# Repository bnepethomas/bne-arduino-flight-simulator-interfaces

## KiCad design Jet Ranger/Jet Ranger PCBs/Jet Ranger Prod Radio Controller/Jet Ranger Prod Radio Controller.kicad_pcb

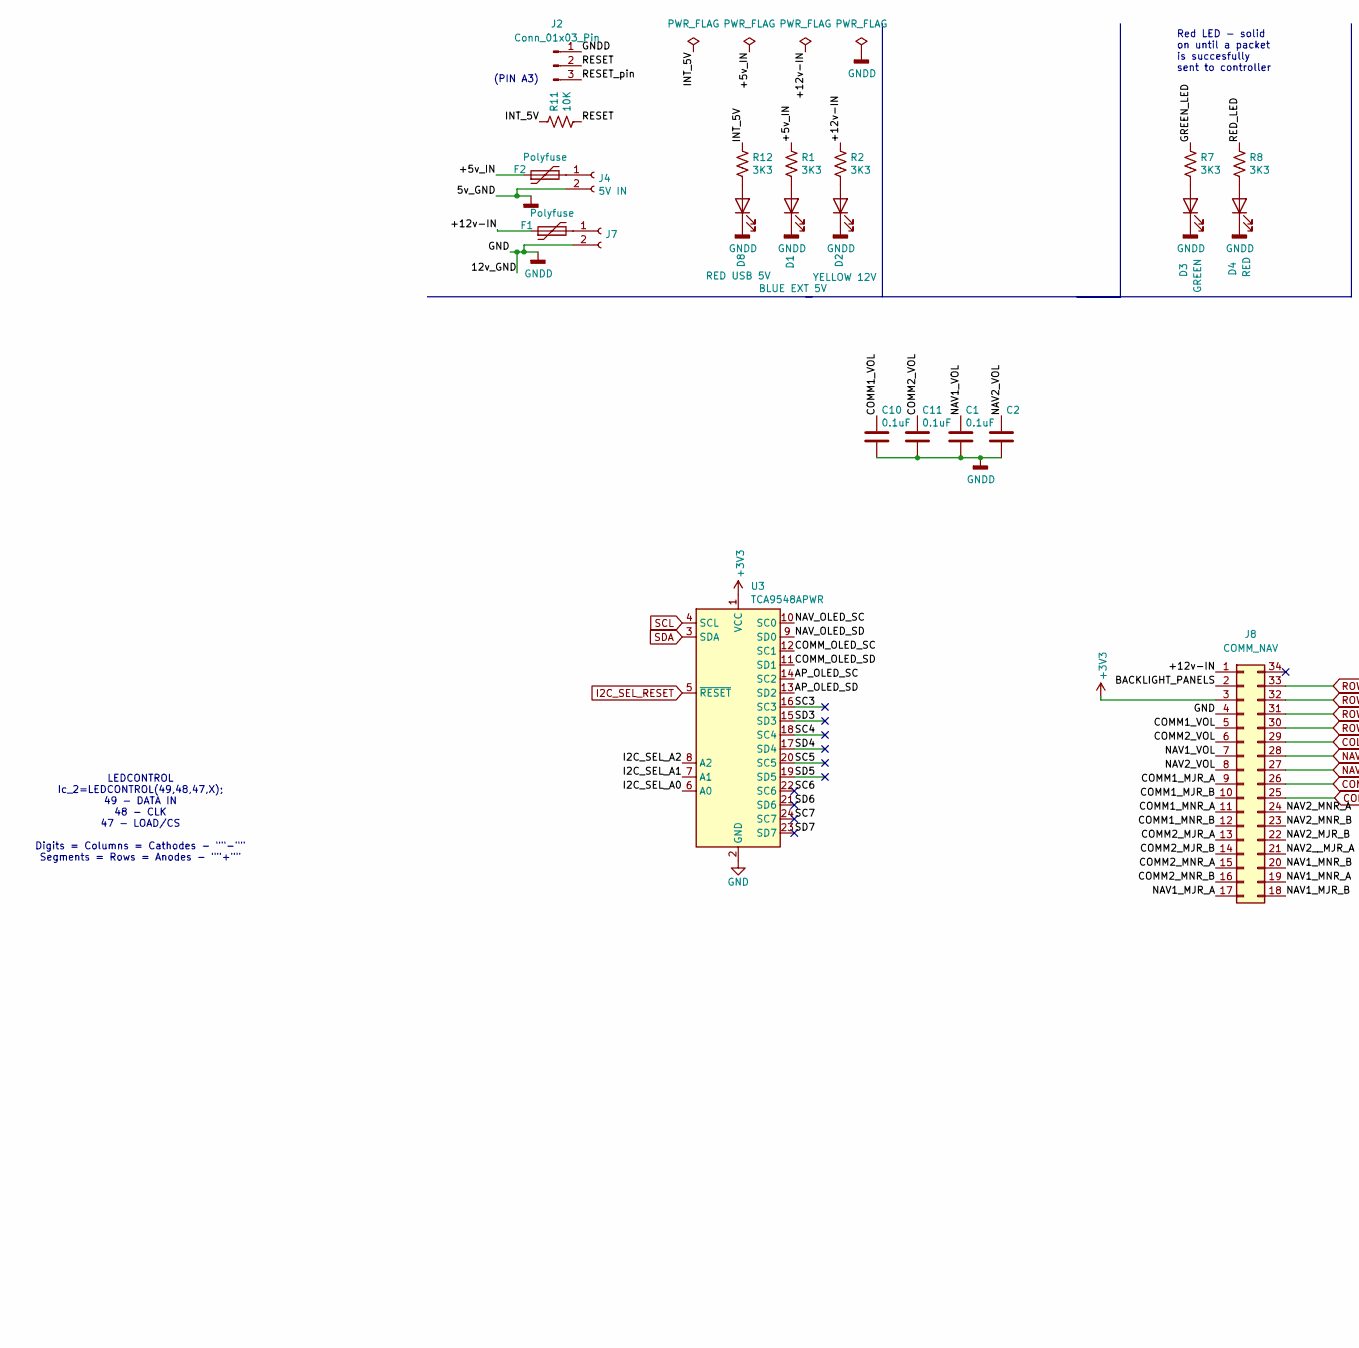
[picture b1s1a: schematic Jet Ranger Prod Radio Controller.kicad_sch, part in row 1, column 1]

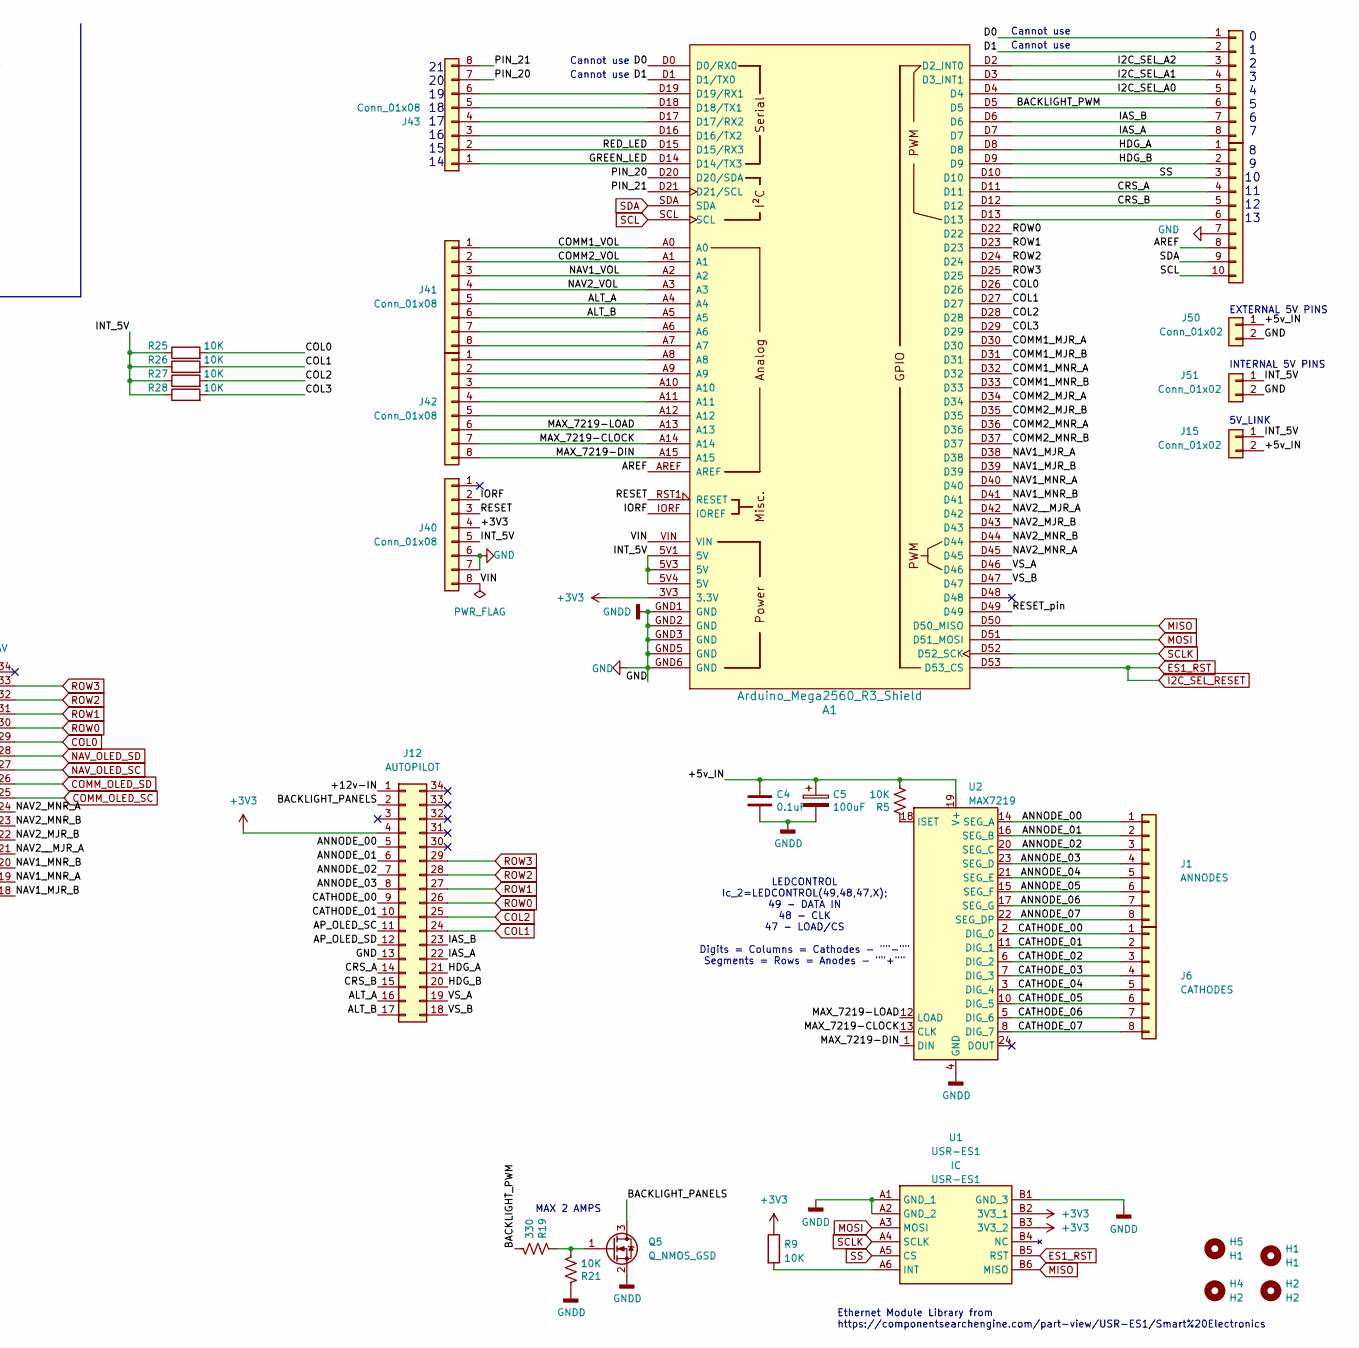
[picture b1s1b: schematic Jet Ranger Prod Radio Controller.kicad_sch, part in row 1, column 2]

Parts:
A1: Arduino_Mega2560_R3_Shield
C1, C2, C4, C10, C11: 0.1uF; C_Disc_D3.0mm_W2.0mm_P2.50mm
C5: 100uF; C_Radial_D8.0mm_H7.0mm_P3.50mm
D1: BLUE EXT 5V; LED_D3.0mm
D2: YELLOW 12V; LED_D3.0mm
D3: GREEN; LED_D3.0mm
D4: RED; LED_D3.0mm
D8: RED USB 5V; LED_D3.0mm
F1, F2: Polyfuse; Fuse_Littelfuse_395Series
H1, H5: H1; MountingHole_3.2mm_M3
H2, H4: H2; MountingHole_3.2mm_M3
J1: ANNODES; PinHeader_1x08_P2.54mm_Vertical
J2: Conn_01x03_Pin; PinHeader_1x03_P2.54mm_Vertical
J4: 5V IN; BarrelJack_Horizontal
J6: CATHODES; PinHeader_1x08_P2.54mm_Vertical
J7: STEPPER IN 12-20VDC; BarrelJack_Horizontal
J8: COMM_NAV; IDC-Header_2x17_P2.54mm_Vertical
J12: AUTOPILOT; IDC-Header_2x17_P2.54mm_Vertical
J15, J50, J51: Conn_01x02; PinHeader_1x02_P2.54mm_Vertical
J40, J41, J42, J43, J44: Conn_01x08; PinHeader_1x08_P2.54mm_Vertical
J45: Conn_01x10; PinHeader_1x10_P2.54mm_Vertical
Q5: Q_NMOS_GSD; TO-220-3_Vertical
R1, R2, R7, R8, R12: 3K3; R_Axial_DIN0207_L6.3mm_D2.5mm_P2.54mm_Vertical
R5, R9, R11, R21, R25, R26, R27, R28: 10K; R_Axial_DIN0207_L6.3mm_D2.5mm_P2.54mm_Vertical
R19: 330; R_Axial_DIN0207_L6.3mm_D2.5mm_P2.54mm_Vertical
U1: USR-ES1; USRES1; Manufacturer_Part_Number USR-ES1
U2: MAX7219; DIP-24_W7.62mm_LongPads
U3: TCA9548APWR; AllieExpress_TCA9548A

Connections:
+3V3: A1.3V3 (3.3V), J8.3, J12.4, J40.4, R9.1, U1.B2 (3V3_1), U1.B3 (3V3_2), U3.1 (VCC)
/+5v_IN: C4.1, C5.1, F2.1, J15.2, J50.1, R1.1, R5.2, U2.19 (V+)
/+12v-IN: F1.1, J8.1, J12.1, R2.1
/ALT_A: A1.A4, J12.16, J41.5
/ALT_B: A1.A5, J12.17, J41.6
/ANNODE_00: J1.1, J12.5, U2.14 (SEG_A)
/ANNODE_01: J1.2, J12.6, U2.16 (SEG_B)
/ANNODE_02: J1.3, J12.7, U2.20 (SEG_C)
/ANNODE_03: J1.4, J12.8, U2.23 (SEG_D)
/ANNODE_04: J1.5, U2.21 (SEG_E)
/ANNODE_05: J1.6, U2.15 (SEG_F)
/ANNODE_06: J1.7, U2.17 (SEG_G)
/ANNODE_07: J1.8, U2.22 (SEG_DP)
/AP_OLED_SC: J12.11, U3.14 (SC2)
/AP_OLED_SD: J12.12, U3.13 (SD2)
/AREF: A1.AREF, J45.8
/BACKLIGHT_PANELS: J8.2, J12.2, Q5.3 (D)
/BACKLIGHT_PWM: A1.D5, J44.6, R19.2
/CATHODE_00: J6.1, J12.9, U2.2 (DIG_0)
/CATHODE_01: J6.2, J12.10, U2.11 (DIG_1)
/CATHODE_02: J6.3, U2.6 (DIG_2)
/CATHODE_03: J6.4, U2.7 (DIG_3)
/CATHODE_04: J6.5, U2.3 (DIG_4)
/CATHODE_05: J6.6, U2.10 (DIG_5)
/CATHODE_06: J6.7, U2.5 (DIG_6)
/CATHODE_07: J6.8, U2.8 (DIG_7)
/COL3: A1.D29, R28.2
/COMM1_MJR_A: A1.D30, J8.9
/COMM1_MJR_B: A1.D31, J8.10
/COMM1_MNR_A: A1.D32, J8.11
/COMM1_MNR_B: A1.D33, J8.12
/COMM1_VOL: A1.A0, C10.1, J8.5, J41.1
/COMM2_MJR_A: A1.D34, J8.13
/COMM2_MJR_B: A1.D35, J8.14
/COMM2_MNR_A: A1.D36, J8.15
/COMM2_MNR_B: A1.D37, J8.16
/COMM2_VOL: A1.A1, C11.1, J8.6, J41.2
/CRS_A: A1.D11, J12.14, J45.4
/CRS_B: A1.D12, J12.15, J45.5
/D0: A1.D0 (D0/RX0), J44.1
/D1: A1.D1 (D1/TX0), J44.2
/GREEN_LED: A1.D14 (D14/TX3), J43.1, R7.1
/HDG_A: A1.D8, J12.21, J45.1
/HDG_B: A1.D9, J12.20, J45.2
/I2C_SEL_A0: A1.D4, J44.5, U3.6 (A0)
/I2C_SEL_A1: A1.D3 (D3_INT1), J44.4, U3.7 (A1)
/I2C_SEL_A2: A1.D2 (D2_INT0), J44.3, U3.8 (A2)
/IAS_A: A1.D7, J12.22, J44.8
/IAS_B: A1.D6, J12.23, J44.7
/INT_5V: A1.5V1 (5V), A1.5V3 (5V), A1.5V4 (5V), J15.1, J40.5, J51.1, R11.1, R12.1, R25.1, R26.1, R27.1, R28.1
/IORF: A1.IORF (IOREF), J40.2
/MAX_7219-CLOCK: A1.A14, J42.7, U2.13 (CLK)
/MAX_7219-DIN: A1.A15, J42.8, U2.1 (DIN)
/MAX_7219-LOAD: A1.A13, J42.6, U2.12 (LOAD)
/NAV1_MJR_A: A1.D38, J8.17
/NAV1_MJR_B: A1.D39, J8.18
/NAV1_MNR_A: A1.D40, J8.19
/NAV1_MNR_B: A1.D41, J8.20
/NAV1_VOL: A1.A2, C1.1, J8.7, J41.3
/NAV2_MJR_B: A1.D43, J8.22
/NAV2_MNR_A: A1.D45, J8.24
/NAV2_MNR_B: A1.D44, J8.23
/NAV2_VOL: A1.A3, C2.1, J8.8, J41.4
/NAV2__MJR_A: A1.D42, J8.21
/PIN_20: A1.D20 (D20/SDA), J43.7
/PIN_21: A1.D21 (D21/SCL), J43.8
/RED_LED: A1.D15 (D15/RX3), J43.2, R8.1
/RESET: A1.RST1 (RESET), J2.2, J40.3, R11.2
/RESET_pin: A1.D49, J2.3
/SC3: U3.16 (SC3)
/SC4: U3.18 (SC4)
/SC5: U3.20 (SC5)
/SC6: U3.22 (SC6)
/SC7: U3.24 (SC7)
/SD3: U3.15 (SD3)
/SD4: U3.17 (SD4)
/SD5: U3.19 (SD5)
/SD6: U3.21 (SD6)
/SD7: U3.23 (SD7)
/VIN: A1.VIN, J40.8
/VS_A: A1.D46, J12.19
/VS_B: A1.D47, J12.18
COL0: A1.D26, J8.29, R25.2
COL1: A1.D27, J12.24, R26.2
COL2: A1.D28, J12.25, R27.2
COMM_OLED_SC: J8.25, U3.12 (SC1)
COMM_OLED_SD: J8.26, U3.11 (SD1)
ES1_RST: A1.D53 (D53_CS), U1.B5 (RST), U3.5 (~RESET)
GND: A1.GND1 (GND), A1.GND2 (GND), A1.GND3 (GND), A1.GND5 (GND), A1.GND6 (GND), C1.2, C2.2, C4.2, C5.2, C10.2, C11.2, D1.1 (K), D2.1 (K), D3.1 (K), D4.1 (K), D8.1 (K), J2.1, J4.2, J7.2, J8.4, J12.13, J40.6, J40.7, J45.7, J50.2, J51.2, Q5.2 (S), R21.1, U1.A1 (GND_1), U1.A2 (GND_2), U1.B1 (GND_3), U2.4 (GND), U2.9 (GND), U3.2 (GND)
MISO: A1.D50 (D50_MISO), U1.B6 (MISO)
MOSI: A1.D51 (D51_MOSI), U1.A3 (MOSI)
NAV_OLED_SC: J8.27, U3.10 (SC0)
NAV_OLED_SD: J8.28, U3.9 (SD0)
unnamed: A1.D16 (D16/TX2), J43.3
unnamed: A1.D17 (D17/RX2), J43.4
unnamed: A1.D18 (D18/TX1), J43.5
unnamed: A1.D19 (D19/RX1), J43.6
unnamed: D1.2 (A), R1.2
unnamed: D2.2 (A), R2.2
unnamed: D3.2 (A), R7.2
unnamed: D4.2 (A), R8.2
unnamed: D8.2 (A), R12.2
unnamed: F2.2, J4.1
unnamed: F1.2, J7.1
unnamed: A1.A6, J41.7
unnamed: A1.A7, J41.8
unnamed: A1.A8, J42.1
unnamed: A1.A9, J42.2
unnamed: A1.A10, J42.3
unnamed: A1.A11, J42.4
unnamed: A1.A12, J42.5
unnamed: A1.D13, J45.6
unnamed: Q5.1 (G), R19.1, R21.2
unnamed: R9.2, U1.A6 (INT)
unnamed: R5.1, U2.18 (ISET)
ROW0: A1.D22, J8.30, J12.26
ROW1: A1.D23, J8.31, J12.27
ROW2: A1.D24, J8.32, J12.28
ROW3: A1.D25, J8.33, J12.29
SCL: A1.SCL, J45.10, U3.4 (SCL)
SCLK: A1.D52 (D52_SCK), U1.A4 (SCLK)
SDA: A1.SDA, J45.9, U3.3 (SDA)
SS: A1.D10, J45.3, U1.A5 (CS)

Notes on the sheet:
MAX 2 AMPS
INTERNAL 5V PINS
Ethernet Module Library from https://componentsearchengine.com/part-view/USR-ES1/Smart%20Electronics
LEDCONTROL Ic_2=LEDCONTROL(49,48,47,X); 49 - DATA IN 48 - CLK 47 - LOAD/CS Digits = Columns = Cathodes - ""-"" Segments = Rows = Anodes - ""+""
Cannot use
(PIN A3)
0 1 2 3 4 5 6 7
Red LED - solid on until a packet is succesfully sent to controller
5V_LINK
21 20 19 18 17 16 15 14
EXTERNAL 5V PINS
8 9 10 11 12 13

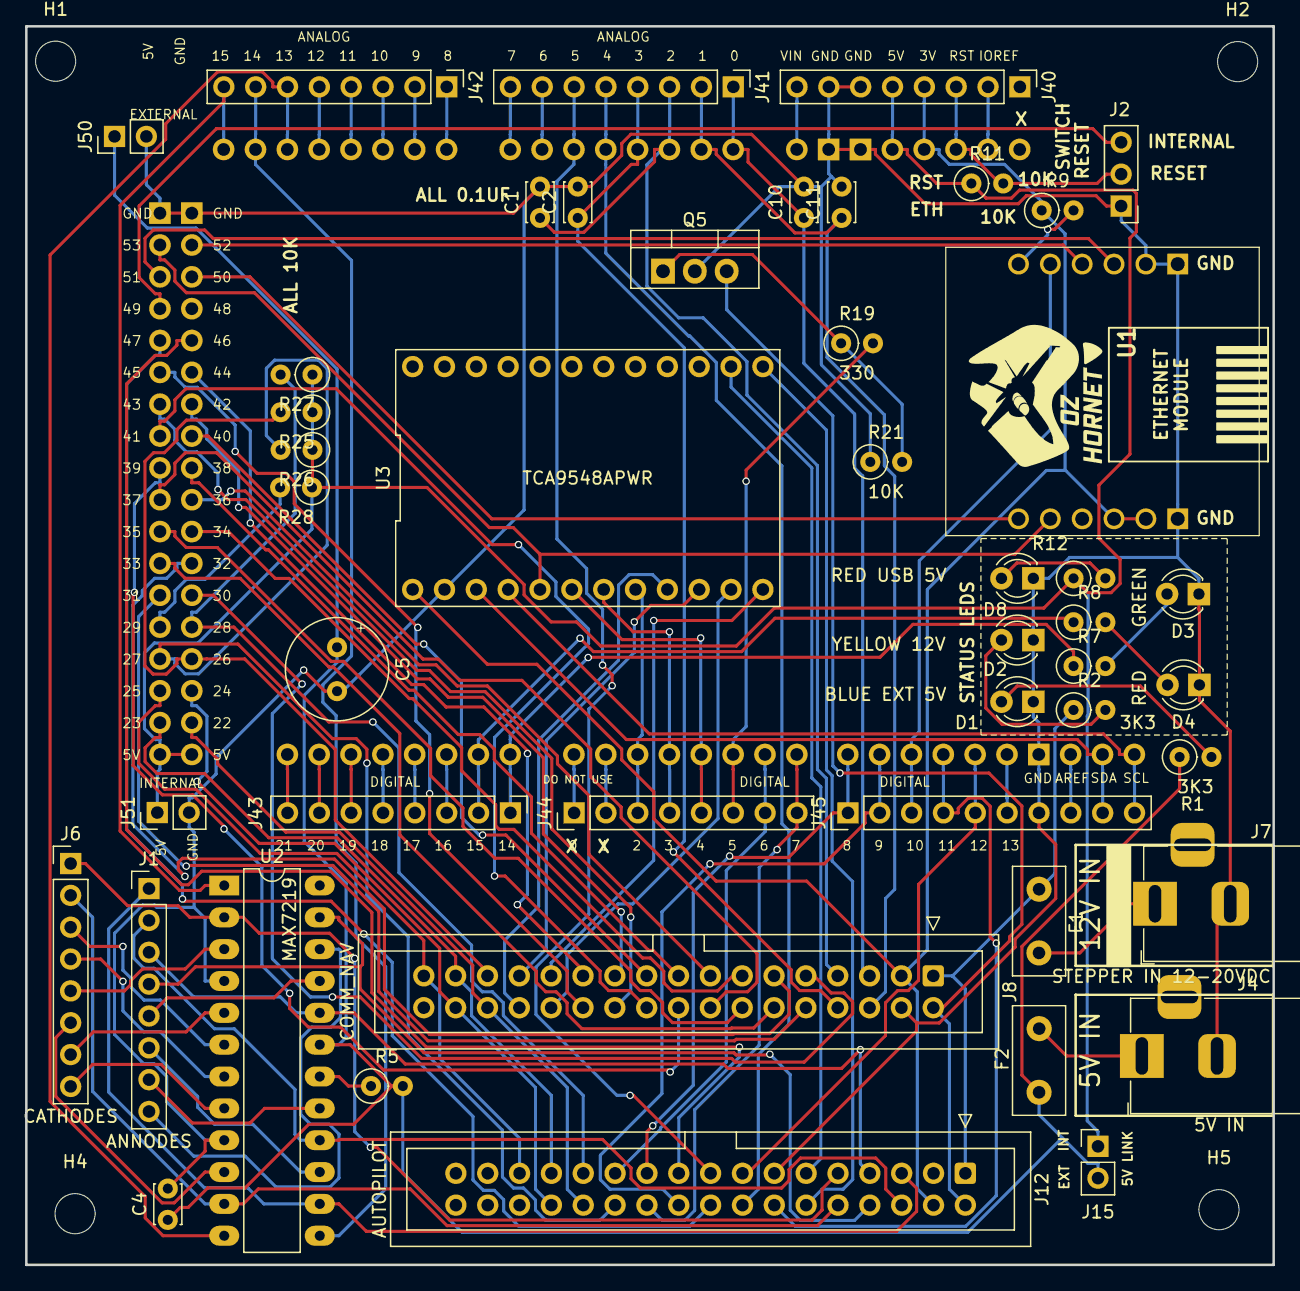
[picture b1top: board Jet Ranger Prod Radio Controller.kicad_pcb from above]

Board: 2 copper layers, 99.5 x 98.8 mm, 52 parts (0 on the bottom side), 113 nets.

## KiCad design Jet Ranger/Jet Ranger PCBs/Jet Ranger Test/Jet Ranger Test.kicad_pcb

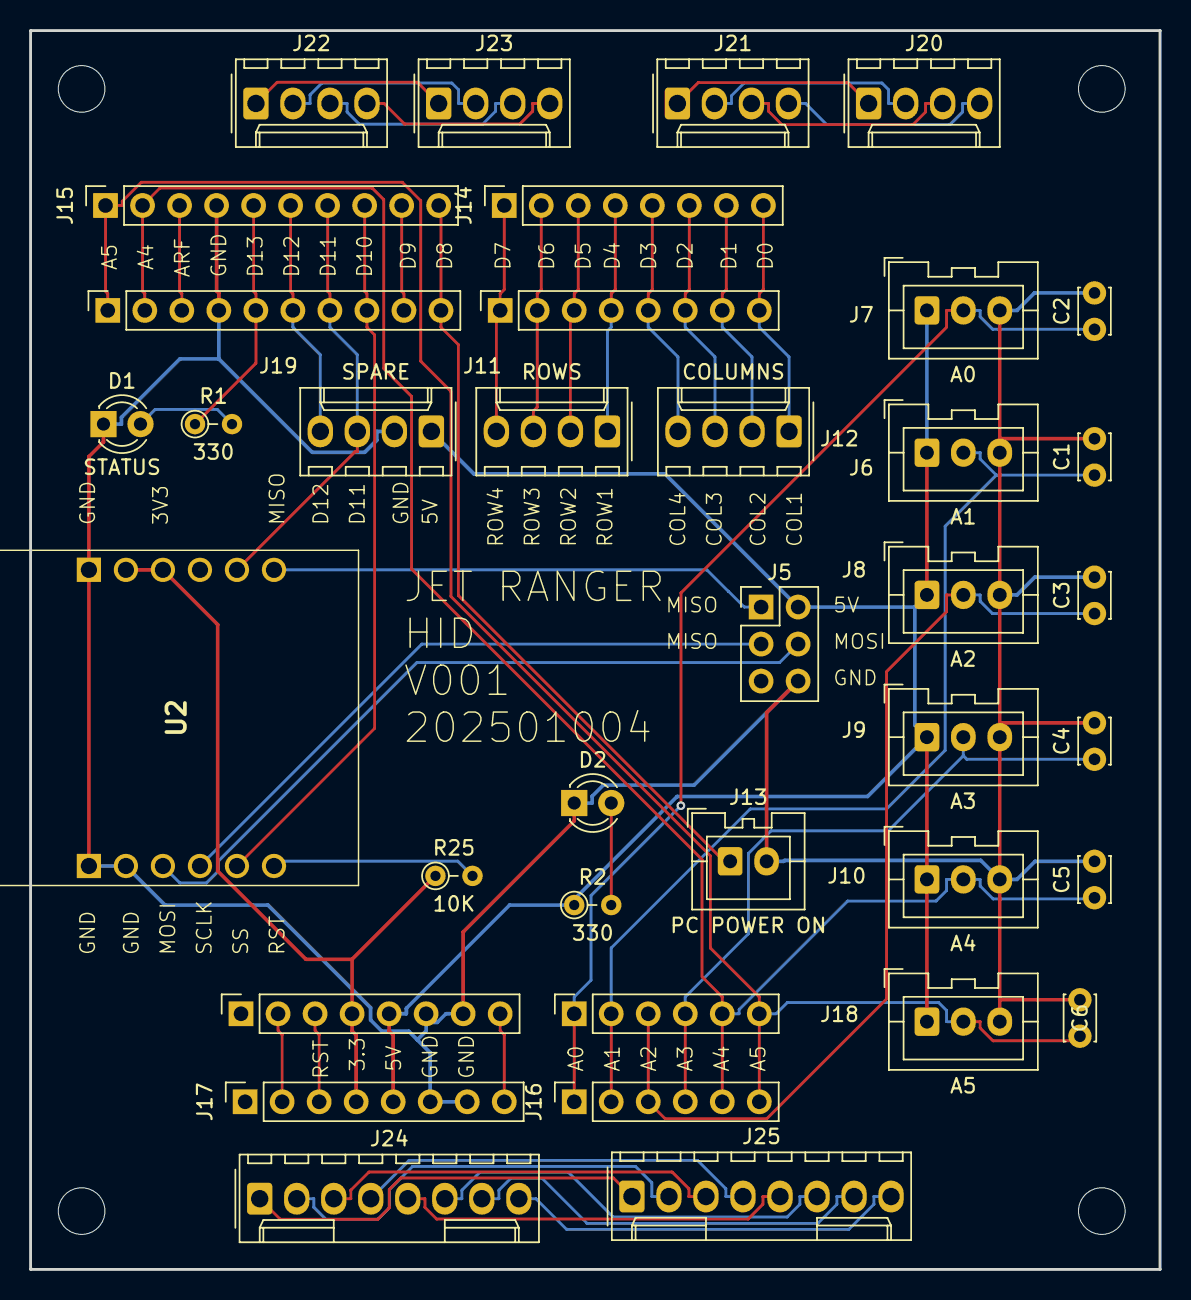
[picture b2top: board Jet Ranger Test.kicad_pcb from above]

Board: 2 copper layers, 77.5 x 85.0 mm, 41 parts (0 on the bottom side), 49 nets.

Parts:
C1, C2, C3, C4, C5, C6: 0.1uF; C_Disc_D3.0mm_W2.0mm_P2.50mm
D1: STATUS; LED_D3.0mm_FlatTop
D2: 5V; LED_D3.0mm_FlatTop
H1, H2, H3, H4: MountingHole; MountingHole_3.2mm_M3
J1, J17: Power; PinSocket_1x08_P2.54mm_Vertical
J2, J15: Digital/PWM; PinSocket_1x10_P2.54mm_Vertical
J3, J16: Analog; PinSocket_1x06_P2.54mm_Vertical
J4, J14: Digital/PWM; PinSocket_1x08_P2.54mm_Vertical
J5: ICSP; PinHeader_2x03_P2.54mm_Vertical
J6: A1; JST_XA_B03B-XASK-1_1x03_P2.50mm_Vertical
J7: A0; JST_XA_B03B-XASK-1_1x03_P2.50mm_Vertical
J8: A2; JST_XA_B03B-XASK-1_1x03_P2.50mm_Vertical
J9: A3; JST_XA_B03B-XASK-1_1x03_P2.50mm_Vertical
J10: A4; JST_XA_B03B-XASK-1_1x03_P2.50mm_Vertical
J11: ROWS; Molex_KK-254_AE-6410-04A_1x04_P2.54mm_Vertical
J12: COLUMNS; Molex_KK-254_AE-6410-04A_1x04_P2.54mm_Vertical
J13: PC POWER ON; JST_XA_B02B-XASK-1_1x02_P2.50mm_Vertical
J18: A5; JST_XA_B03B-XASK-1_1x03_P2.50mm_Vertical
J19, J20, J21, J22, J23: SPARE; Molex_KK-254_AE-6410-04A_1x04_P2.54mm_Vertical
J24, J25: SPARE; Molex_KK-254_AE-6410-08A_1x08_P2.54mm_Vertical
R1, R2: 330; R_Axial_DIN0204_L3.6mm_D1.6mm_P2.54mm_Vertical
R25: 10K; R_Axial_DIN0204_L3.6mm_D1.6mm_P2.54mm_Vertical
U2: USR-ES1; USRES1

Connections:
+3V3: J1.4, J17.4, R25.1, U2.B2 (3V3_1), U2.B3 (3V3_2)
+5V: J1.5, J5.2, J6.1, J7.1, J8.1, J9.1, J10.1, J17.5, J18.1, J19.1, R2.1
/2: J4.6, J12.3, J14.6
/4: J4.4, J11.1, J14.4
/7: J4.1, J11.4, J14.1
/8: J2.10, J13.1, J15.10
/12: J2.6, J15.6, J19.4
/13: J2.5, J15.5, R1.1
/*3: J4.5, J12.4, J14.5
/*5: J4.3, J11.2, J14.3
/*6: J4.2, J11.3, J14.2
/*9: J2.9, J15.9
/A0: C2.1, J3.1, J7.2, J16.1
/A1: C1.1, J3.2, J6.2, J16.2
/A2: C3.1, J3.3, J8.2, J16.3
/A3: C4.1, J3.4, J9.2, J16.4
/A4: C5.1, J2.2, J3.5, J10.2, J15.2, J16.5
/A5: C6.1, J2.1, J3.6, J15.1, J16.6, J18.2
/AREF: J2.3, J15.3
/COL1: J4.8, J12.1, J14.8
/COL2: J4.7, J12.2, J14.7
/IOREF: J1.2, J17.2
/~RESET: J1.3, J17.3
ES1_RST: J2.7, J15.7, J19.3, U2.B5 (RST)
GND: C1.2, C2.2, C3.2, C4.2, C5.2, C6.2, D1.1 (K), D2.1 (K), J1.6, J1.7, J2.4, J5.6, J6.3, J7.3, J8.3, J9.3, J10.3, J13.2, J15.4, J17.6, J17.7, J18.3, J19.2, U2.A1 (GND_1), U2.A2 (GND_2), U2.B1 (GND_3)
MISO: J5.1, U2.B6 (MISO)
MOSI: J5.4, U2.A3 (MOSI)
unnamed: D1.2 (A), R1.2
unnamed: D2.2 (A), R2.2
unnamed: J20.1, J21.1
unnamed: J20.2, J21.2
unnamed: J20.3, J21.3
unnamed: J20.4, J21.4
unnamed: J22.1, J23.1
unnamed: J22.2, J23.2
unnamed: J22.3, J23.3
unnamed: J22.4, J23.4
unnamed: J24.1, J25.1
unnamed: J24.2, J25.2
unnamed: J24.3, J25.3
unnamed: J24.4, J25.4
unnamed: J24.5, J25.5
unnamed: J24.6, J25.6
unnamed: J24.7, J25.7
unnamed: J24.8, J25.8
unnamed: R25.2, U2.A6 (INT)
SCLK: J5.3, U2.A4 (SCLK)
SS: J2.8, J15.8, U2.A5 (CS)
VCC: J1.8, J17.8

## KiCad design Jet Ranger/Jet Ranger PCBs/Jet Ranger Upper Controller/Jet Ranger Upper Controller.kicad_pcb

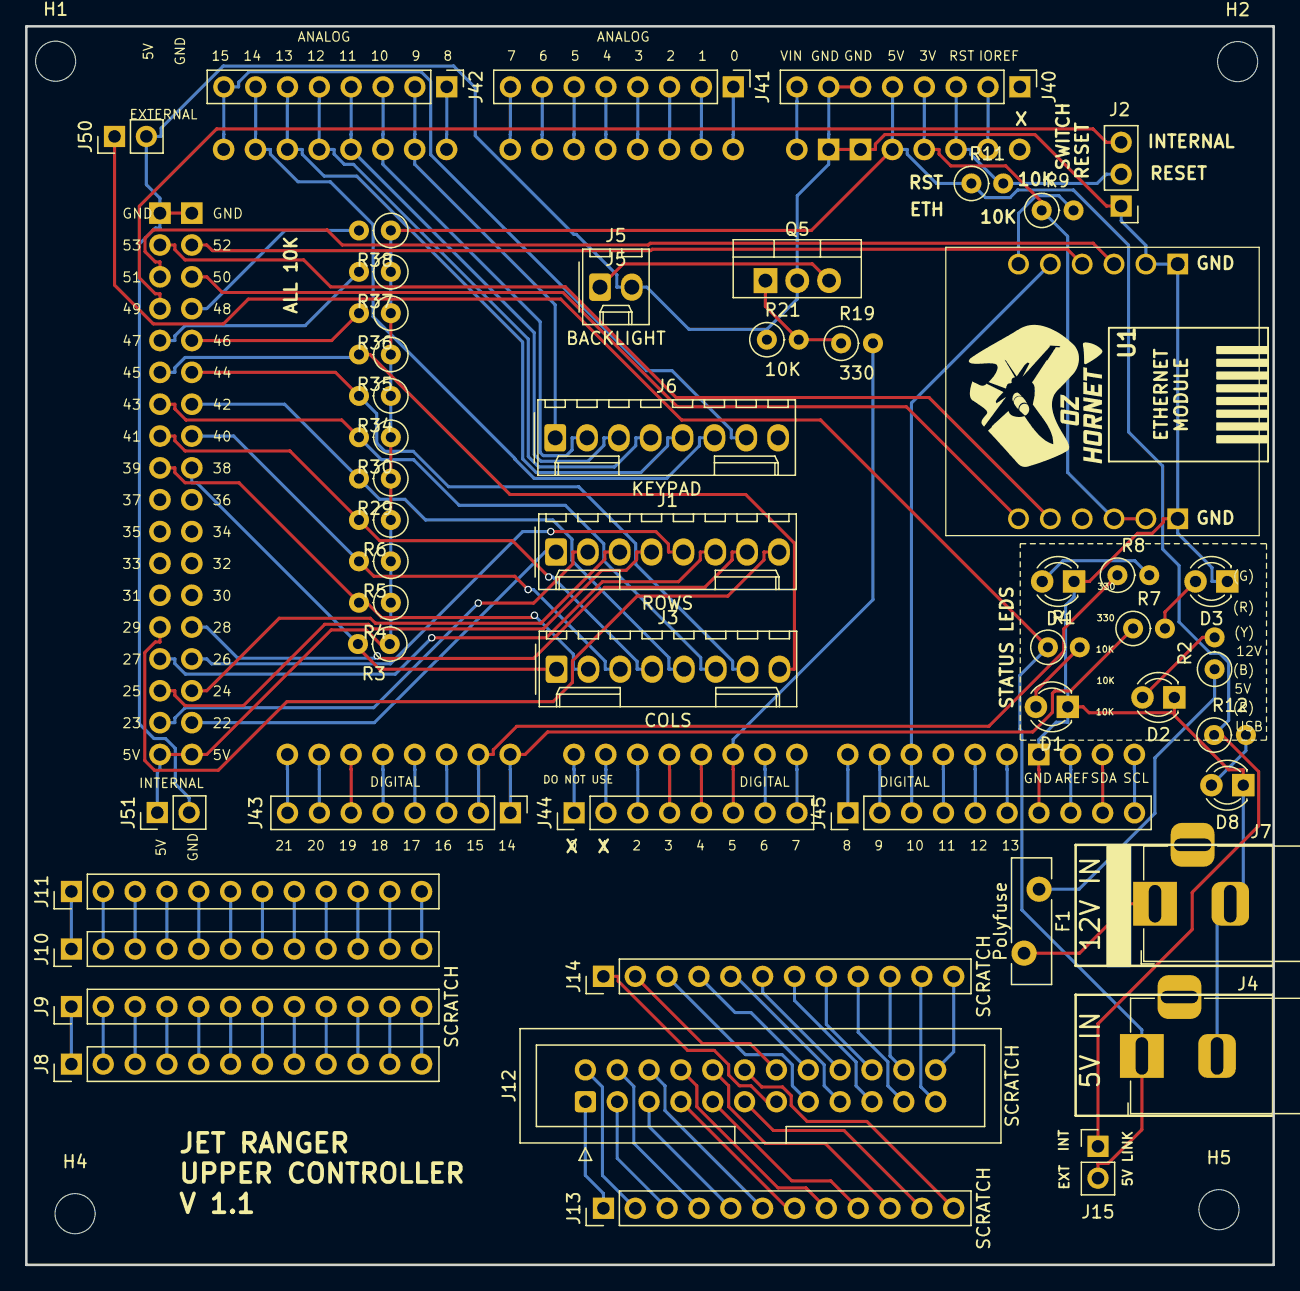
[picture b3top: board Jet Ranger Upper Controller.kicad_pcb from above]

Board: 2 copper layers, 99.5 x 98.8 mm, 56 parts (0 on the bottom side), 130 nets.

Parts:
A1: Arduino_Mega2560_R3_Shield
D1, D2, D8: LED; LED_D3.0mm
D3: GREEN; LED_D3.0mm
D4: RED; LED_D3.0mm
F1: Polyfuse; Fuse_Bourns_MF-RG400
H1, H5: H1; MountingHole_3.2mm_M3
H2, H4: H2; MountingHole_3.2mm_M3
J1: ROWS; Molex_KK-254_AE-6410-08A_1x08_P2.54mm_Vertical
J2: Conn_01x03_Pin; PinHeader_1x03_P2.54mm_Vertical
J3: COLS; Molex_KK-254_AE-6410-08A_1x08_P2.54mm_Vertical
J4: 5V IN; BarrelJack_Horizontal
J5: BACKLIGHT; Molex_KK-254_AE-6410-02A_1x02_P2.54mm_Vertical
J6: KEYPAD; Molex_KK-254_AE-6410-08A_1x08_P2.54mm_Vertical
J7: STEPPER IN 12-20VDC; BarrelJack_Horizontal
J8, J9, J10, J11, J13, J14: SCRATCH; PinHeader_1x12_P2.54mm_Vertical
J12: SCRATCH; IDC-Header_2x12_P2.54mm_Vertical
J15, J50, J51: Conn_01x02; PinHeader_1x02_P2.54mm_Vertical
J40, J41, J42, J43, J44: Conn_01x08; PinHeader_1x08_P2.54mm_Vertical
J45: Conn_01x10; PinHeader_1x10_P2.54mm_Vertical
Q5: Q_NMOS_GSD; TO-220-3_Vertical
R1, R12: 5K; R_Axial_DIN0207_L6.3mm_D2.5mm_P2.54mm_Vertical
R2, R3, R4, R5, R6, R9, R11, R21, R29, R30, R34, R35, R36, R37, R38: 10K; R_Axial_DIN0207_L6.3mm_D2.5mm_P2.54mm_Vertical
R7, R8, R19: 330; R_Axial_DIN0207_L6.3mm_D2.5mm_P2.54mm_Vertical
U1: USR-ES1; USRES1

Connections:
+3V3: A1.3V3 (3.3V), J40.4, R9.1, U1.B2 (3V3_1), U1.B3 (3V3_2)
/+5v_IN: J4.1, J15.2, J50.1, R1.1
/+12v-IN: F1.1, R2.1
/AREF: A1.AREF, J45.8
/BACKLIGHT_PANELS: J5.1, Q5.3 (D)
/BACKLIGHT_PWM: A1.D5, J44.6, R19.2
/COL0: A1.D38, J3.1, R3.2
/COL1: A1.D39, J3.2, R4.2
/COL2: A1.D40, J3.3, R5.2
/COL3: A1.D41, J3.4, R6.2
/COL4: A1.D42, J3.5, R29.2
/COL5: A1.D43, J3.6, R30.2
/COL6: A1.D44, J3.7, R34.2
/COL7: A1.D45, J3.8, R35.2
/COL8: A1.D46, R36.2
/COL9: A1.D47, R37.2
/COL10: A1.D48, R38.2
/D0: A1.D0 (D0/RX0), J44.1
/D1: A1.D1 (D1/TX0), J44.2
/GPS_TX: A1.D18 (D18/TX1), J43.5
/GREEN_LED: A1.D14 (D14/TX3), J43.1, R7.1
/INT_5V: A1.5V1 (5V), A1.5V3 (5V), A1.5V4 (5V), J15.1, J40.5, J51.1, R3.1, R4.1, R5.1, R6.1, R11.1, R12.1, R29.1, R30.1, R34.1, R35.1, R36.1, R37.1, R38.1
/IORF: A1.IORF (IOREF), J40.2
/KEYPAD_1: A1.A9, J6.1, J42.2
/KEYPAD_2: A1.A10, J6.2, J42.3
/KEYPAD_3: A1.A11, J6.3, J42.4
/KEYPAD_4: A1.A12, J6.4, J42.5
/KEYPAD_5: A1.A13, J6.5, J42.6
/KEYPAD_6: A1.A14, J6.6, J42.7
/KEYPAD_7: A1.A15, J6.7, J42.8
/PIN_20: A1.D20 (D20/SDA), J43.7
/PIN_21: A1.D21 (D21/SCL), J43.8
/RED_LED: A1.D15 (D15/RX3), J43.2, R8.1
/RESET: A1.RST1 (RESET), J2.2, J40.3, R11.2
/RESET_pin: A1.D49, J2.3
/ROW0: A1.D22, J1.1
/ROW1: A1.D23, J1.2
/ROW2: A1.D24, J1.3
/ROW3: A1.D25, J1.4
/ROW4: A1.D26, J1.5
/ROW5: A1.D27, J1.6
/ROW6: A1.D28, J1.7
/ROW7: A1.D29, J1.8
/VIN: A1.VIN, J40.8
ES1_RST: A1.D53 (D53_CS), U1.B5 (RST)
GND: A1.GND1 (GND), A1.GND2 (GND), A1.GND3 (GND), A1.GND5 (GND), A1.GND6 (GND), D1.1 (K), D2.1 (K), D3.1 (K), D4.1 (K), D8.1 (K), J2.1, J4.2, J5.2, J7.2, J40.6, J40.7, J45.7, J50.2, J51.2, Q5.2 (S), R21.1, U1.A1 (GND_1), U1.A2 (GND_2), U1.B1 (GND_3)
MISO: A1.D50 (D50_MISO), U1.B6 (MISO)
MOSI: A1.D51 (D51_MOSI), U1.A3 (MOSI)
unnamed: A1.D2 (D2_INT0), J44.3
unnamed: A1.D3 (D3_INT1), J44.4
unnamed: A1.D16 (D16/TX2), J43.3
unnamed: A1.D17 (D17/RX2), J43.4
unnamed: A1.D19 (D19/RX1), J43.6
unnamed: D1.2 (A), R1.2
unnamed: D2.2 (A), R2.2
unnamed: D3.2 (A), R7.2
unnamed: D4.2 (A), R8.2
unnamed: D8.2 (A), R12.2
unnamed: F1.2, J7.1
unnamed: J8.1, J9.1
unnamed: J8.2, J9.2
unnamed: J8.3, J9.3
unnamed: J8.4, J9.4
unnamed: J8.5, J9.5
unnamed: J8.6, J9.6
unnamed: J8.7, J9.7
unnamed: J8.8, J9.8
unnamed: J8.9, J9.9
unnamed: J8.10, J9.10
unnamed: J8.11, J9.11
unnamed: J8.12, J9.12
unnamed: J10.1, J11.1
unnamed: J10.2, J11.2
unnamed: J10.3, J11.3
unnamed: J10.4, J11.4
unnamed: J10.5, J11.5
unnamed: J10.6, J11.6
unnamed: J10.7, J11.7
unnamed: J10.8, J11.8
unnamed: J10.9, J11.9
unnamed: J10.10, J11.10
unnamed: J10.11, J11.11
unnamed: J10.12, J11.12
unnamed: J12.1, J13.1
unnamed: J12.2, J13.2
unnamed: J12.3, J13.3
unnamed: J12.4, J13.4
unnamed: J12.5, J13.5
unnamed: J12.6, J13.6
unnamed: J12.7, J13.7
unnamed: J12.8, J13.8
unnamed: J12.9, J13.9
unnamed: J12.10, J13.10
unnamed: J12.11, J13.11
unnamed: J12.12, J13.12
unnamed: J12.13, J14.1
unnamed: J12.14, J14.2
unnamed: J12.15, J14.3
unnamed: J12.16, J14.4
unnamed: J12.17, J14.5
unnamed: J12.18, J14.6
unnamed: J12.19, J14.7
unnamed: J12.20, J14.8
unnamed: J12.21, J14.9
unnamed: J12.22, J14.10
unnamed: J12.23, J14.11
unnamed: J12.24, J14.12
unnamed: A1.A0, J41.1
unnamed: A1.A1, J41.2
unnamed: A1.A2, J41.3
unnamed: A1.A3, J41.4
unnamed: A1.A4, J41.5
unnamed: A1.A5, J41.6
unnamed: A1.A6, J41.7
unnamed: A1.A7, J41.8
unnamed: A1.A8, J42.1
unnamed: A1.D4, J44.5
unnamed: A1.D6, J44.7
unnamed: A1.D7, J44.8
unnamed: A1.D8, J45.1
unnamed: A1.D9, J45.2
unnamed: A1.D11, J45.4
unnamed: A1.D12, J45.5
unnamed: A1.D13, J45.6
unnamed: Q5.1 (G), R19.1, R21.2
unnamed: R9.2, U1.A6 (INT)
SCL: A1.SCL, J45.10
SCLK: A1.D52 (D52_SCK), U1.A4 (SCLK)
SDA: A1.SDA, J45.9
SS: A1.D10, J45.3, U1.A5 (CS)

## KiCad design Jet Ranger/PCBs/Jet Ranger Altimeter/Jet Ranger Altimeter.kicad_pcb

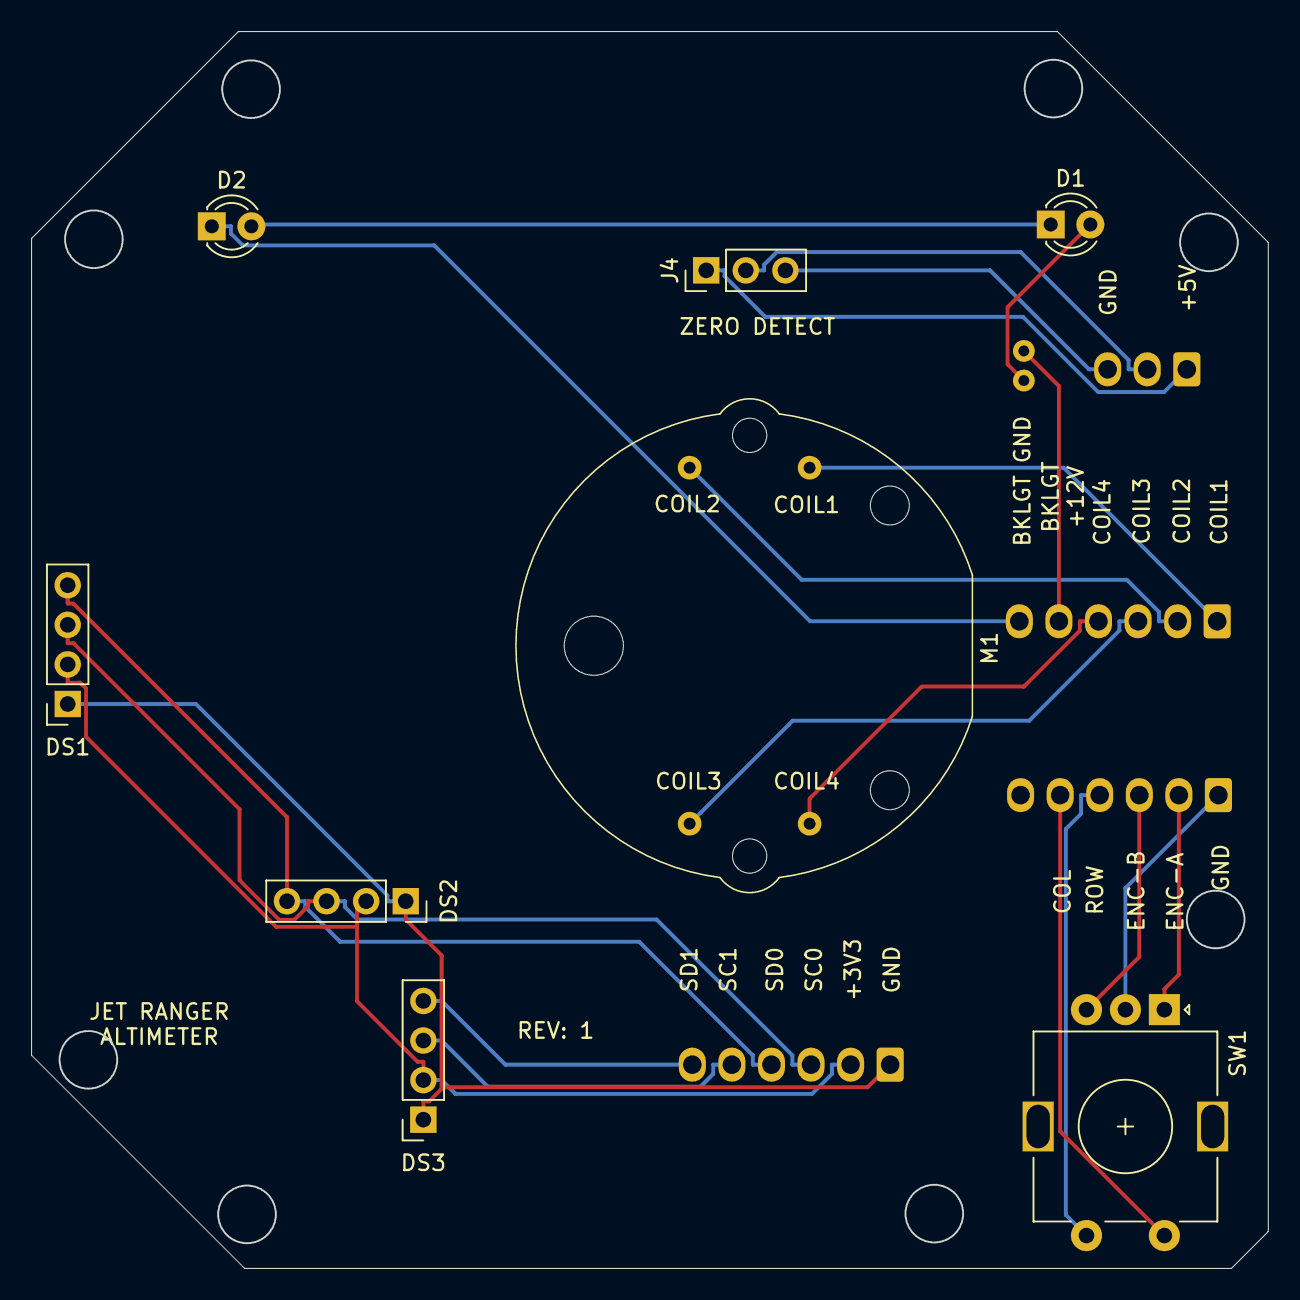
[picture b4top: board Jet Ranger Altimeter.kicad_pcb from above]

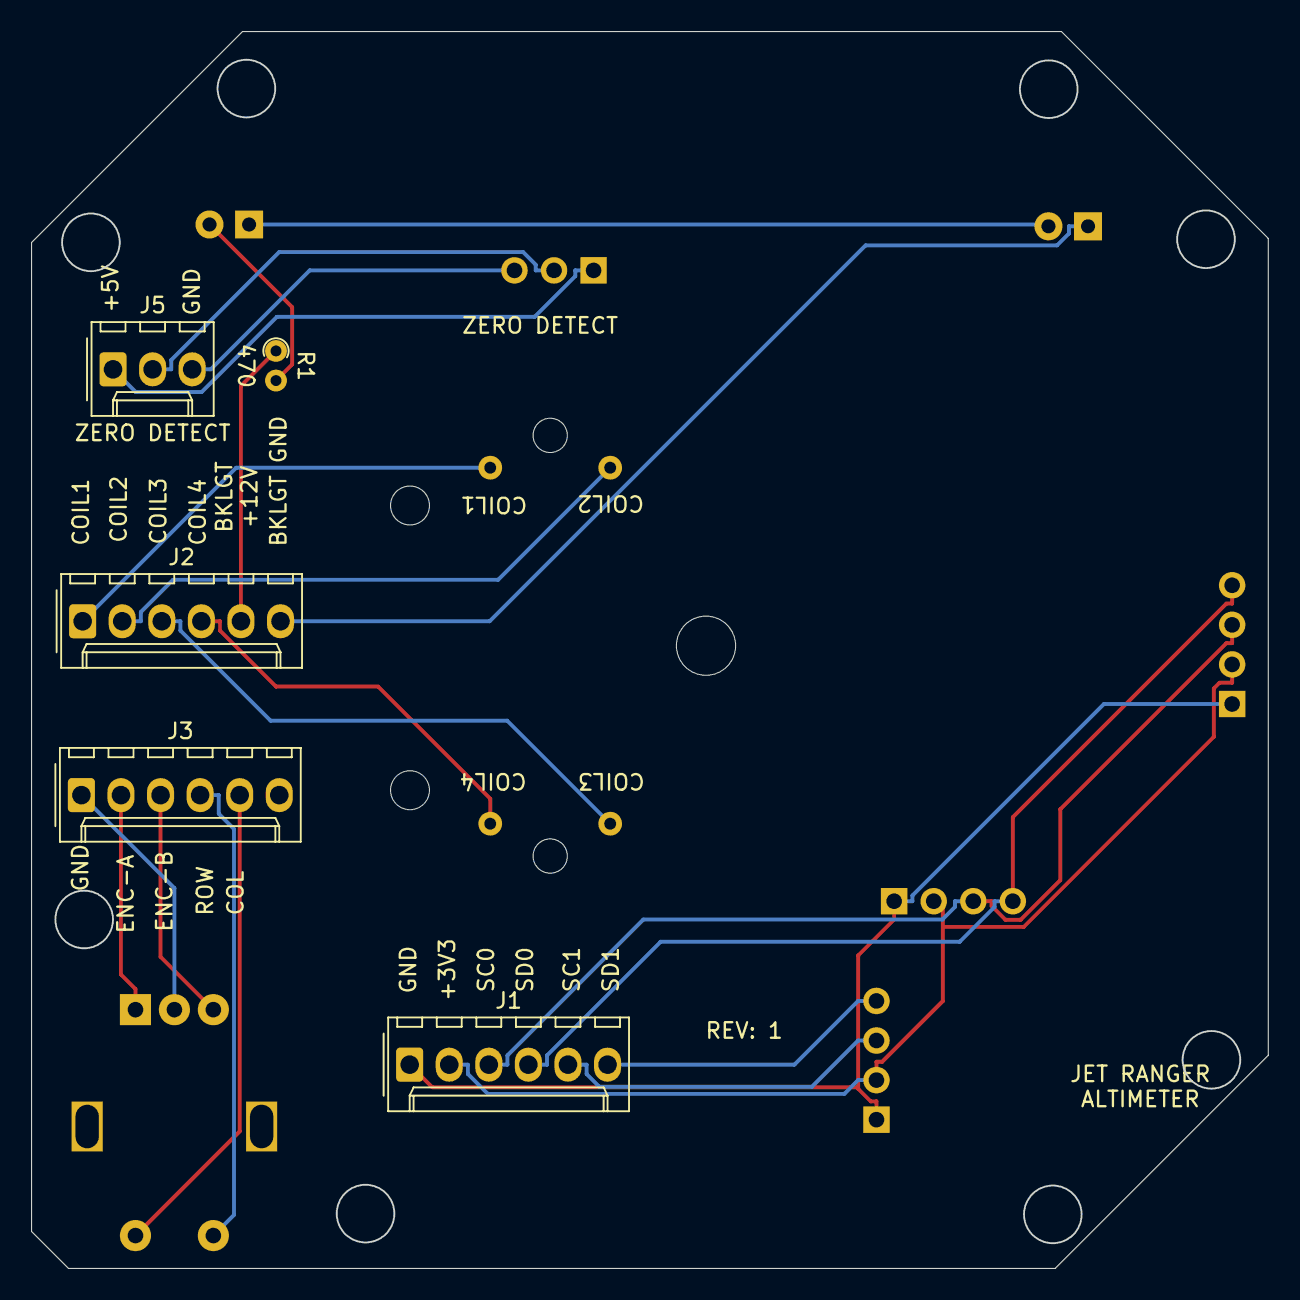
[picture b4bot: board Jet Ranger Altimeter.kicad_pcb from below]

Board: 2 copper layers, 79.4 x 79.4 mm, 13 parts (5 on the bottom side), 22 nets.

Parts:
D1, D2: LED; LED_D3.0mm
DS1, DS2: 10K_ALT_DISP; PinSocket_1x04_P2.54mm_Vertical
DS3: PRESS_DISP; PinSocket_1x04_P2.54mm_Vertical
J1: OLED; Molex_KK-254_AE-6410-06A_1x06_P2.54mm_Vertical
J2: STEPPER; Molex_KK-254_AE-6410-06A_1x06_P2.54mm_Vertical
J3: ENCODER; Molex_KK-254_AE-6410-06A_1x06_P2.54mm_Vertical
J4: ZERO; PinHeader_1x03_P2.54mm_Vertical
J5: ZERO DETECT; Molex_KK-254_AE-6410-03A_1x03_P2.54mm_Vertical
M1: VID29-02
R1: 470; R_Axial_DIN0204_L3.6mm_D1.6mm_P1.90mm_Vertical
SW1: RotaryEncoder_Switch; RotaryEncoder_Alps_EC11E-Switch_Vertical_H20mm

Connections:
+3V3: DS1.2, DS2.2, DS3.2, J1.2
+5V: J4.1, J5.1
/BACKLIGHT_+12V: J2.5, R1.1
/BACKLIGHT_GND: D2.1 (K), J2.6
/COIL1: J2.1, M1.1
/COIL2: J2.2, M1.2 (-)
/COIL3: J2.3, M1.3
/COIL4: J2.4, M1.4
/COL: J3.5, SW1.S2
/ENCODER B: J3.3, SW1.B
/ENCODER-A: J3.2, SW1.A
/ENCORDER GND: J3.1, SW1.C
/ROW: J3.4, SW1.S1
/SC0: DS1.3, DS2.3, J1.3
/SC1: DS3.3, J1.5
/SD0: DS1.4, DS2.4, J1.4
/SD1: DS3.4, J1.6
/ZERO_DETECT: J4.2, J5.2
GND: DS1.1, DS2.1, DS3.1, J1.1
GND1: J4.3, J5.3
unnamed: D1.2 (A), R1.2
unnamed: D1.1 (K), D2.2 (A)

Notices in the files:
Jet Ranger/Jet Ranger PCBs/Jet Ranger Prod Radio Controller/Jet Ranger Prod Radio Controller.kicad_pcb:
© OZ HORNET
